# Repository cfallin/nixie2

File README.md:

# GPS-synchronized Nixie tube clock

This is a custom-designed (custom circuit design / PCB boards and custom
microcontroller firmware) digital clock. It receives the time from a GPS
receiver board, adjusts for an user-selectable timezone, and displays the time
on "Nixie tubes". A [nixie tube](https://en.wikipedia.org/wiki/Nixie_tube) is a
cold-cathode vacuum tube display technology: it uses high voltage (about 160
volts in this design) applied to an electrode in the shape of a digit in order
to display a number in brilliant glowing orange. It really is quite
mesmerizing!

This repo contains custom circuit board layouts for the main clock board and a
separate adapter sub-board for each Nixie tube. The sub-boards are designed for
IN-14 tubes (which can currently be found on eBay or Etsy for ~$20 each), but
could be adapted for IN-12, IN-18, or some other size.

The main board contains an AVR ATmega8 microcontroller, a 20MHz crystal,
several 74HC595 shift registers to expand the AVR's IO, and six KI155ID1
open-collector high voltage driver chips.

The board interfaces with a separate high-voltage DC-DC power supply, because
designing such a supply to be efficient is quite hard and I do not possess the
analog black magic skills! I bought [this
one](https://www.amazon.com/gp/product/B09D94N3MX) for $11. You can substitute
any suitable source of ~160V DC rated for about 4mA per tube (24mA total, or
just under 4 watts).

GPS is also black magic, so I bought a pre-designed GPS receiver module
[here](https://www.amazon.com/gp/product/B07P8YMVNT) for $12, and an external
active antenna [here](https://www.amazon.com/gp/product/B083D59N55) for $11.
The module provides a 1Hz "pulse-per-second" precision output and a 9600bps
serial line providing time, position, and satellite lock information using the
[NMEA](https://en.wikipedia.org/wiki/NMEA_0183) protocol. You can substitute
any GPS receiver that provides a PPS output and NMEA signal.

The ATmega8 runs firmware that decodes the NMEA to get an initial time
(synchronizing whenever a valid NMEA packet with a timestamp is received). It
measures the internal crystal oscillator against the PPS and then ticks based
on the main CPU clock, calibrated with this ticks-per-PPS value. This allows
the clock to receive the time when GPS signal is available, learn how fast or
slow its own internal oscillator is running, and then continue to keep time
when the GPS signal is lost. Whenever it comes back, time will resynchronize
automatically.

There is a simple user interface consisting of four buttons. The leftmost (SW4
on the main board) switches between time mode and set-timezone mode. In the
latter, SW2 decrements TZ offset hour and SW1 increments TZ offset hour.
(Half-hour or 15 minute timezone offsets are not yet supported; I know these
timezones exist, sorry! Happy to take PRs if anyone in such a timezone builds
this clock!)

Total cost for the clock, not including the one-time tool purchases I made
(e.g. an AVR programmer) or the scrap wood, glue, etc. for the very janky base,
and definitely not including my time, was about $230:

- $42 for the PCBs (mainboard and 6x nixie tube adapters) at Aisler.net
- $90 for the six IN-14s, on Etsy
- $22 for the KI155ID1 driver chips
- $12 for the GPS receiver
- $11 for the GPS antenna
- $11 for the 160V DC supply
- about $40 for the ATmega8, 20MHz crystal, 74HC595s, a few resistors and
  capacitors, pin headers, wire, etc.

I started thinking about building a Nixie clock in 2014, but started working on
this design regularly in Nov 2021. It first displayed a GPS-synchronized time
on Jan 6, 2022. I'd like to improve the UI a bit (allow a non-GPS
locally-set-time mode as well), and definitely improve the casing, but it suits
me well enough for now! I finally know what time it is!

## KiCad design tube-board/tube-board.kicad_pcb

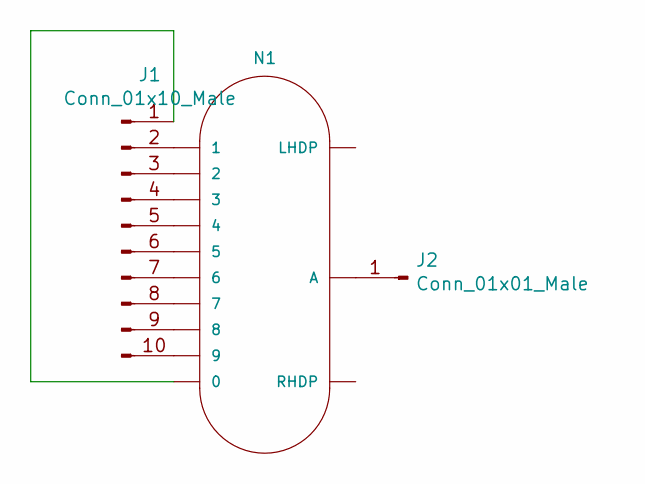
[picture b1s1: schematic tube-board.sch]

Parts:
J1: Conn_01x10_Male; PinHeader_1x10_P2.54mm_Vertical
J2: Conn_01x01_Male; PinHeader_1x01_P2.54mm_Vertical
N1: IN-14

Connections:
unnamed: J1.1, N1.0
unnamed: J1.2, N1.1
unnamed: J1.3, N1.2
unnamed: J1.4, N1.3
unnamed: J1.5, N1.4
unnamed: J1.6, N1.5
unnamed: J1.7, N1.6
unnamed: J1.8, N1.7
unnamed: J1.9, N1.8
unnamed: J1.10, N1.9
unnamed: J2.1, N1.A

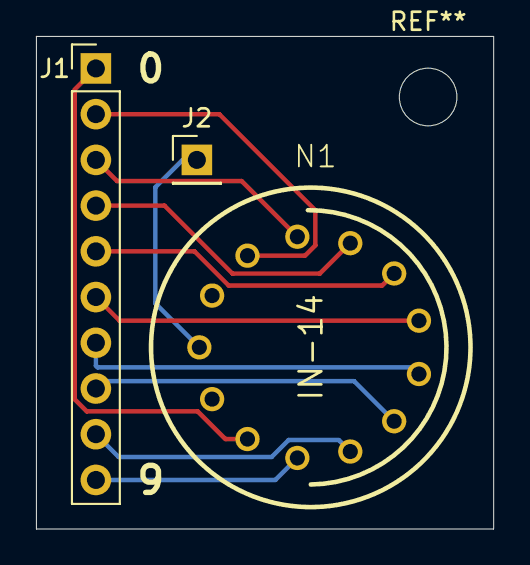
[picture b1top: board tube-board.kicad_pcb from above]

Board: 2 copper layers, 25.4 x 27.4 mm, 3 parts (0 on the bottom side), 11 nets.

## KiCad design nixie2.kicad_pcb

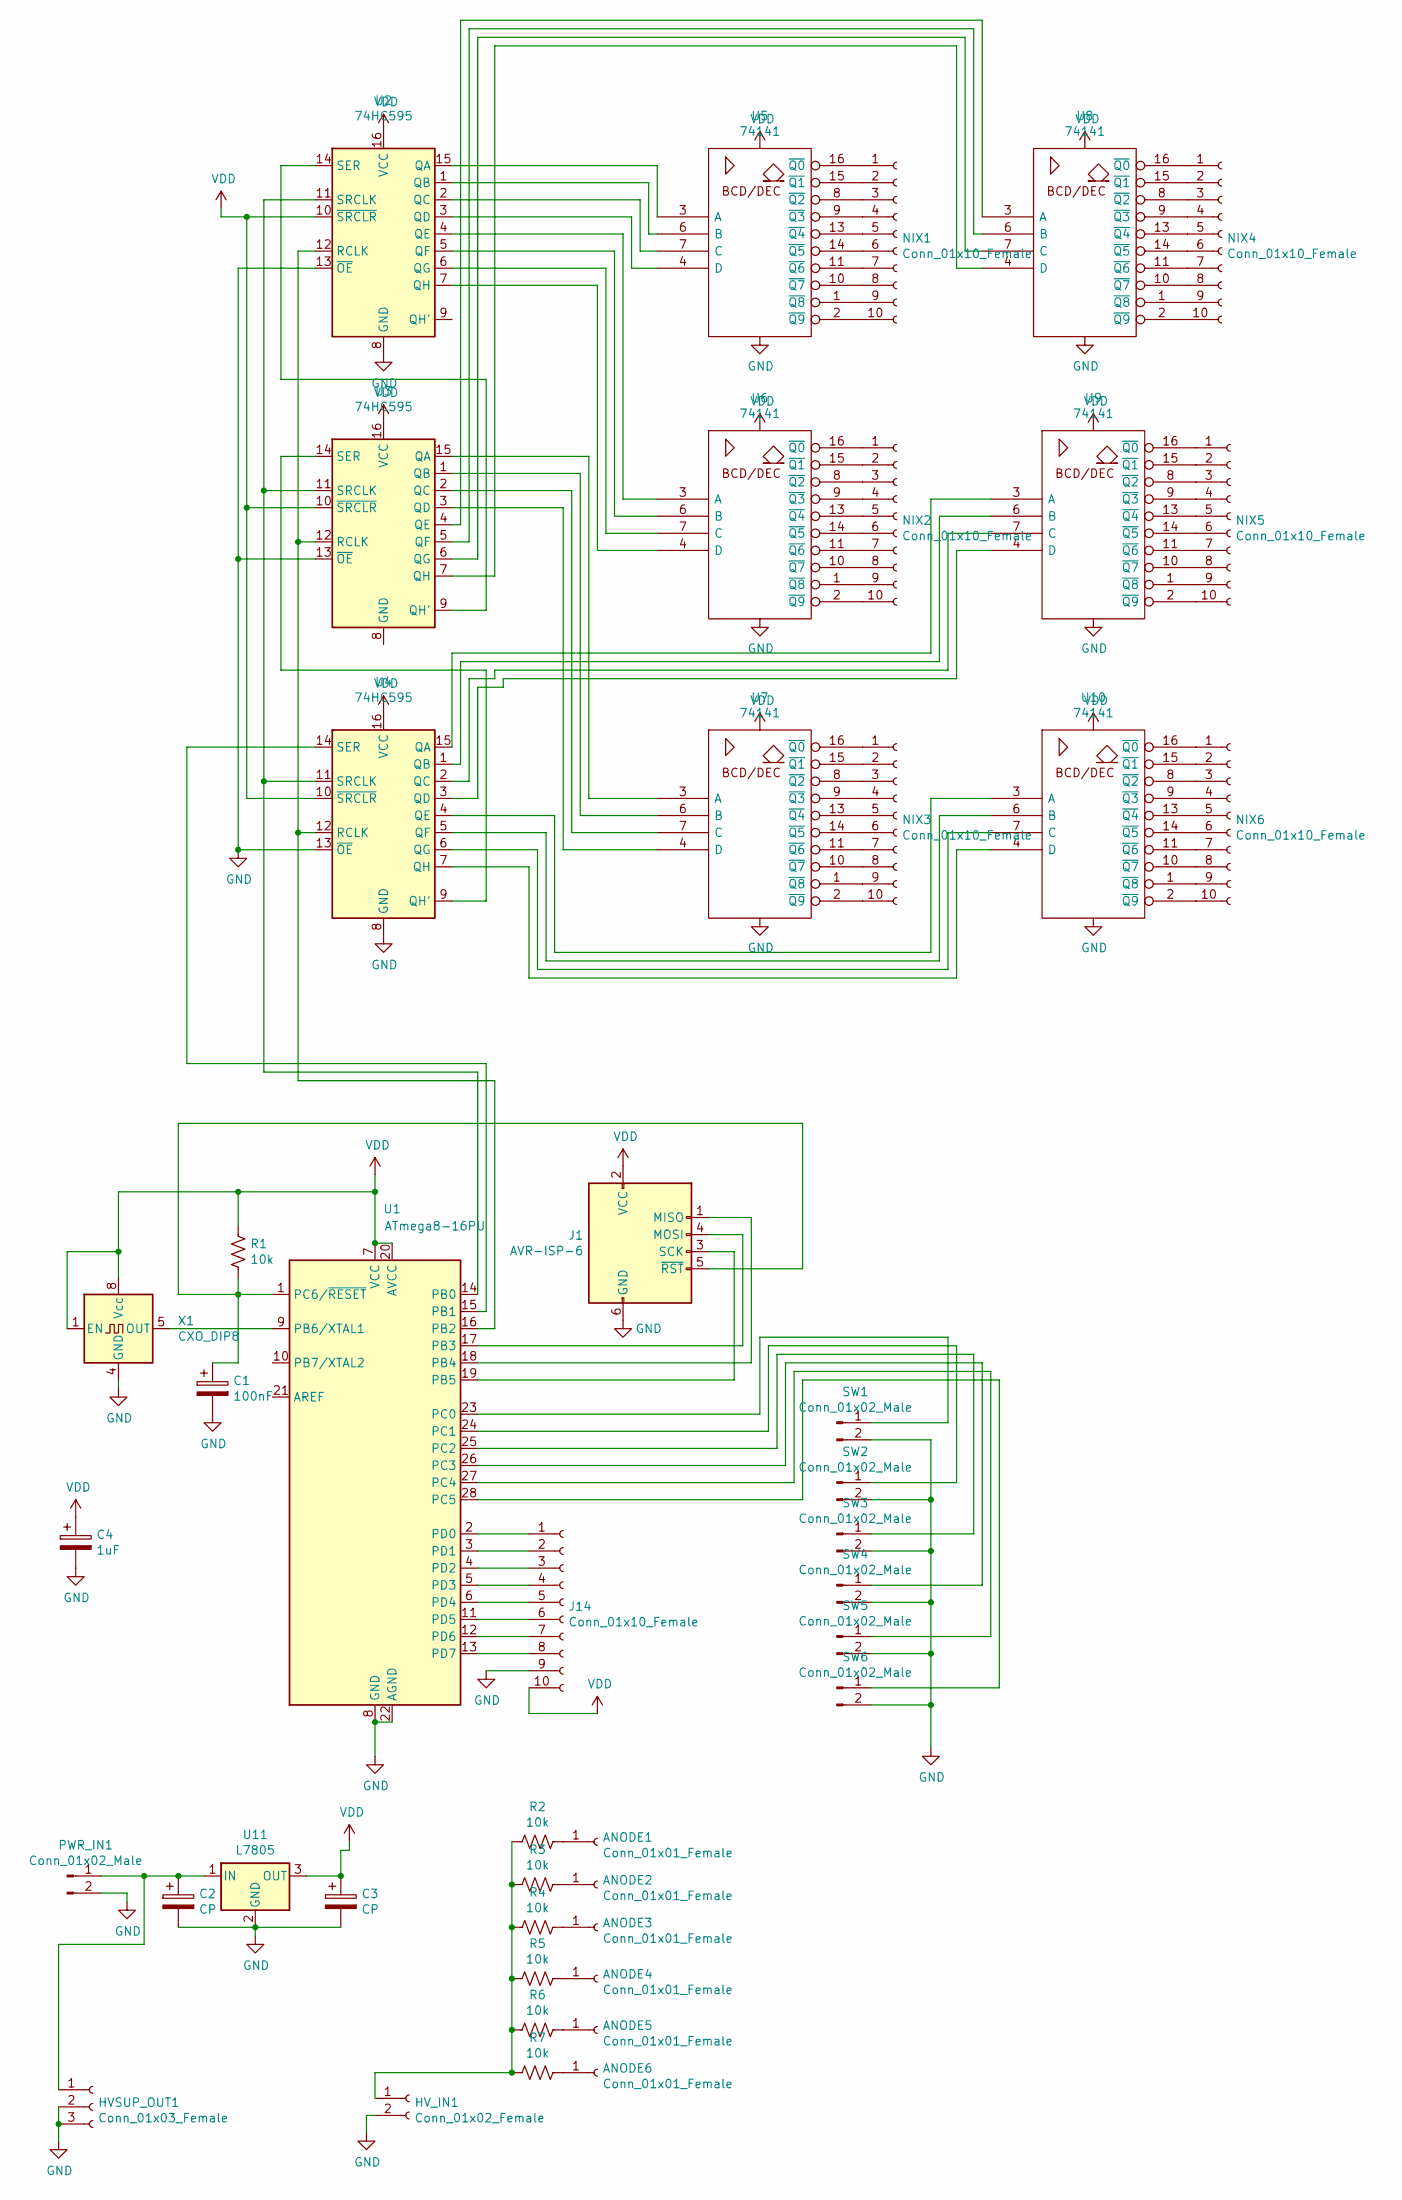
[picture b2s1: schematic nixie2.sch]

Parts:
ANODE1, ANODE2, ANODE3, ANODE4, ANODE5, ANODE6: Conn_01x01_Female; PinHeader_1x01_P2.54mm_Vertical
C1: 100nF; CP_Radial_Tantal_D5.5mm_P2.50mm
C2, C3: CP; CP_Radial_D10.0mm_P2.50mm
C4: 1uF; CP_Radial_D4.0mm_P1.50mm
HVSUP_OUT1: Conn_01x03_Female; PinHeader_1x03_P2.54mm_Vertical
HV_IN1: Conn_01x02_Female; PinHeader_1x02_P2.54mm_Vertical
J1: AVR-ISP-6; PinHeader_2x03_P2.54mm_Vertical
J14: Conn_01x10_Female; PinHeader_1x10_P2.54mm_Vertical
NIX1, NIX2, NIX3, NIX4, NIX5, NIX6: Conn_01x10_Female; PinHeader_1x10_P2.54mm_Vertical
PWR_IN1: Conn_01x02_Male; PinHeader_1x02_P2.54mm_Vertical
R1: 10k; R_Axial_DIN0207_L6.3mm_D2.5mm_P2.54mm_Vertical
R2, R3, R4, R5, R6, R7: 10k; R_Axial_DIN0207_L6.3mm_D2.5mm_P7.62mm_Horizontal
SW1, SW2, SW3, SW4, SW5, SW6: Conn_01x02_Male; PinHeader_1x02_P2.54mm_Vertical
U1: ATmega8-16PU; DIP-28_W7.62mm
U2, U3, U4: 74HC595; DIP-16_W7.62mm
U5, U6, U7, U8, U9, U10: 74141; DIP-16_W7.62mm
U11: L7805; TO-220-3_Vertical
X1: CXO_DIP8; Oscillator_DIP-8

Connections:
GND: C1.2, C2.2, C3.2, C4.2, HVSUP_OUT1.2, HVSUP_OUT1.3, HV_IN1.2, J1.6 (GND), J14.9, PWR_IN1.2, SW1.2, SW2.2, SW3.2, SW4.2, SW5.2, SW6.2, U1.8 (GND), U1.22 (AGND), U2.8 (GND), U2.13 (~OE), U3.13 (~OE), U4.8 (GND), U4.13 (~OE), U5.12 (GND), U6.12 (GND), U7.12 (GND), U8.12 (GND), U9.12 (GND), U10.12 (GND), U11.2 (GND), X1.4 (GND)
unnamed: ANODE1.1, R2.1
unnamed: ANODE2.1, R3.1
unnamed: ANODE3.1, R4.1
unnamed: ANODE4.1, R5.1
unnamed: ANODE5.1, R6.1
unnamed: ANODE6.1, R7.1
unnamed: C1.1, J1.5 (~RST), R1.2, U1.1 (PC6/~RESET)
unnamed: C2.1, HVSUP_OUT1.1, PWR_IN1.1, U11.1 (IN)
unnamed: HV_IN1.1, R2.2, R3.2, R4.2, R5.2, R6.2, R7.2
unnamed: J1.1 (MISO), U1.18 (PB4)
unnamed: J1.3 (SCK), U1.19 (PB5)
unnamed: J1.4 (MOSI), U1.17 (PB3)
unnamed: J14.1, U1.2 (PD0)
unnamed: J14.2, U1.3 (PD1)
unnamed: J14.3, U1.4 (PD2)
unnamed: J14.4, U1.5 (PD3)
unnamed: J14.5, U1.6 (PD4)
unnamed: J14.6, U1.11 (PD5)
unnamed: J14.7, U1.12 (PD6)
unnamed: J14.8, U1.13 (PD7)
unnamed: NIX1.1, U5.16 (~Q0)
unnamed: NIX1.2, U5.15 (~Q1)
unnamed: NIX1.3, U5.8 (~Q2)
unnamed: NIX1.4, U5.9 (~Q3)
unnamed: NIX1.5, U5.13 (~Q4)
unnamed: NIX1.6, U5.14 (~Q5)
unnamed: NIX1.7, U5.11 (~Q6)
unnamed: NIX1.8, U5.10 (~Q7)
unnamed: NIX1.9, U5.1 (~Q8)
unnamed: NIX1.10, U5.2 (~Q9)
unnamed: NIX2.1, U6.16 (~Q0)
unnamed: NIX2.2, U6.15 (~Q1)
unnamed: NIX2.3, U6.8 (~Q2)
unnamed: NIX2.4, U6.9 (~Q3)
unnamed: NIX2.5, U6.13 (~Q4)
unnamed: NIX2.6, U6.14 (~Q5)
unnamed: NIX2.7, U6.11 (~Q6)
unnamed: NIX2.8, U6.10 (~Q7)
unnamed: NIX2.9, U6.1 (~Q8)
unnamed: NIX2.10, U6.2 (~Q9)
unnamed: NIX3.1, U7.16 (~Q0)
unnamed: NIX3.2, U7.15 (~Q1)
unnamed: NIX3.3, U7.8 (~Q2)
unnamed: NIX3.4, U7.9 (~Q3)
unnamed: NIX3.5, U7.13 (~Q4)
unnamed: NIX3.6, U7.14 (~Q5)
unnamed: NIX3.7, U7.11 (~Q6)
unnamed: NIX3.8, U7.10 (~Q7)
unnamed: NIX3.9, U7.1 (~Q8)
unnamed: NIX3.10, U7.2 (~Q9)
unnamed: NIX4.1, U8.16 (~Q0)
unnamed: NIX4.2, U8.15 (~Q1)
unnamed: NIX4.3, U8.8 (~Q2)
unnamed: NIX4.4, U8.9 (~Q3)
unnamed: NIX4.5, U8.13 (~Q4)
unnamed: NIX4.6, U8.14 (~Q5)
unnamed: NIX4.7, U8.11 (~Q6)
unnamed: NIX4.8, U8.10 (~Q7)
unnamed: NIX4.9, U8.1 (~Q8)
unnamed: NIX4.10, U8.2 (~Q9)
unnamed: NIX5.1, U9.16 (~Q0)
unnamed: NIX5.2, U9.15 (~Q1)
unnamed: NIX5.3, U9.8 (~Q2)
unnamed: NIX5.4, U9.9 (~Q3)
unnamed: NIX5.5, U9.13 (~Q4)
unnamed: NIX5.6, U9.14 (~Q5)
unnamed: NIX5.7, U9.11 (~Q6)
unnamed: NIX5.8, U9.10 (~Q7)
unnamed: NIX5.9, U9.1 (~Q8)
unnamed: NIX5.10, U9.2 (~Q9)
unnamed: NIX6.1, U10.16 (~Q0)
unnamed: NIX6.2, U10.15 (~Q1)
unnamed: NIX6.3, U10.8 (~Q2)
unnamed: NIX6.4, U10.9 (~Q3)
unnamed: NIX6.5, U10.13 (~Q4)
unnamed: NIX6.6, U10.14 (~Q5)
unnamed: NIX6.7, U10.11 (~Q6)
unnamed: NIX6.8, U10.10 (~Q7)
unnamed: NIX6.9, U10.1 (~Q8)
unnamed: NIX6.10, U10.2 (~Q9)
unnamed: SW1.1, U1.23 (PC0)
unnamed: SW2.1, U1.24 (PC1)
unnamed: SW3.1, U1.25 (PC2)
unnamed: SW4.1, U1.26 (PC3)
unnamed: SW5.1, U1.27 (PC4)
unnamed: SW6.1, U1.28 (PC5)
unnamed: U1.9 (PB6/XTAL1), X1.5 (OUT)
unnamed: U1.14 (PB0), U2.11 (SRCLK), U3.11 (SRCLK), U4.11 (SRCLK)
unnamed: U1.15 (PB1), U4.14 (SER)
unnamed: U1.16 (PB2), U2.12 (RCLK), U3.12 (RCLK), U4.12 (RCLK)
unnamed: U2.1 (QB), U5.6 (B)
unnamed: U2.2 (QC), U5.7 (C)
unnamed: U2.3 (QD), U5.4 (D)
unnamed: U2.4 (QE), U6.3 (A)
unnamed: U2.5 (QF), U6.6 (B)
unnamed: U2.6 (QG), U6.7 (C)
unnamed: U2.7 (QH), U6.4 (D)
unnamed: U2.14 (SER), U3.9 (QH')
unnamed: U2.15 (QA), U5.3 (A)
unnamed: U3.1 (QB), U7.6 (B)
unnamed: U3.2 (QC), U7.7 (C)
unnamed: U3.3 (QD), U7.4 (D)
unnamed: U3.4 (QE), U8.3 (A)
unnamed: U3.5 (QF), U8.6 (B)
unnamed: U3.6 (QG), U8.7 (C)
unnamed: U3.7 (QH), U8.4 (D)
unnamed: U3.14 (SER), U4.9 (QH')
unnamed: U3.15 (QA), U7.3 (A)
unnamed: U4.1 (QB), U9.6 (B)
unnamed: U4.2 (QC), U9.7 (C)
unnamed: U4.3 (QD), U9.4 (D)
unnamed: U4.15 (QA), U9.3 (A)
unnamed: U4.4 (QE), U10.3 (A)
unnamed: U4.7 (QH), U10.4 (D)
unnamed: U4.5 (QF), U10.6 (B)
unnamed: U4.6 (QG), U10.7 (C)
VCC: C3.1, C4.1, J1.2 (VCC), J14.10, R1.1, U1.7 (VCC), U1.20 (AVCC), U2.10 (~SRCLR), U2.16 (VCC), U3.10 (~SRCLR), U3.16 (VCC), U4.10 (~SRCLR), U4.16 (VCC), U5.5 (VCC), U6.5 (VCC), U7.5 (VCC), U8.5 (VCC), U9.5 (VCC), U10.5 (VCC), U11.3 (OUT), X1.1 (EN), X1.8 (Vcc)

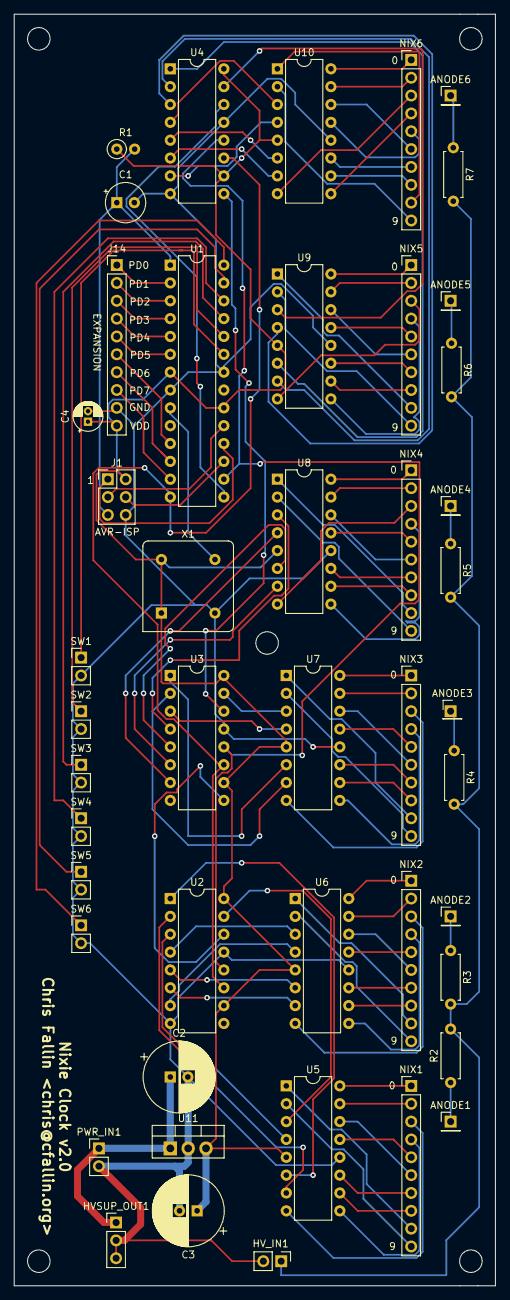
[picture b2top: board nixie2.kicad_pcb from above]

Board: 2 copper layers, 68.5 x 181.0 mm, 46 parts (0 on the bottom side), 118 nets.

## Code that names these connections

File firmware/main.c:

/*
 * Nixie Clock v2.0
 *
 * Copyright (c) 2022 Chris Fallin <chris@cfallin.org>
 * Placed under the Apache-2.0 license.
 */

/* 
 * Assume an ATmega8.
 *
 * IO connections (manufactured board version):
 *
 * PB0 is shift register clock (active high to shift).
 * PB1 is shift register data.
 * PB2 is shift register latch (active high to latch).
 *
 * Shift register output is nixie 2, 1; 4, 3; 6, 5. MSB first of BCD digits.
 *
 * PC0..PC5 are switches 0..5 (to ground; need internal pullups).
 *
 * PD0..PD7 are expansion port.
 */

#include <avr/interrupt.h>

#include "nixie.h"

#define EXPECTED_TIMER_TICKS_PER_SEC 78125 // 20MHz / 256

long timer_ticks = 0;
long hz = EXPECTED_TIMER_TICKS_PER_SEC;
uint8_t time_h = 0, time_m = 0, time_s = 0;

#define DISPLAY_TIME 0
#define DISPLAY_SET 1
#define DISPLAY_CAL 2
int display_mode = 0;

#define UI_TIME 0
#define UI_TO_SET 1
#define UI_SET 2
#define UI_SET_NEXT 3
#define UI_SET_PLUS 4
#define UI_SET_MINUS 5

#define UI_TO_SET_CAL 6
#define UI_SET_CAL 7
#define UI_SET_CAL_NEXT 8
#define UI_SET_CAL_PLUS 9
#define UI_SET_CAL_MINUS 10
#define UI_TO_TIME 11

int ui_state = 0;
int ui_set_digit = 0;

void do_ui() {

    switch (ui_state) {
    case UI_TIME:
        display_mode = DISPLAY_TIME;
        if (switches & 8) {
            ui_state = UI_TO_SET;
        }
        break;
    case UI_TO_SET:
        display_mode = DISPLAY_TIME;
        if (!(switches & 8)) {
            ui_state = UI_SET;
            ui_set_digit = 0;
        }
        break;
    case UI_SET:
        display_mode = DISPLAY_SET;
        if (switches & 8) {
            ui_state = UI_TO_SET_CAL;
        } else if (switches & 4) {
            ui_set_digit++;
            if (ui_set_digit == 3) {
                ui_set_digit = 0;
            }
            ui_state = UI_SET_NEXT;
        } else if (switches & 2) {
            switch (ui_set_digit) {
                case 0:
                    time_h++;
                    if (time_h == 24) {
                        time_h = 0;
                    }
                    break;
                case 1:
                    time_m++;
                    if (time_m == 60) {
                        time_m = 0;
                    }
                    break;
                case 2:
                    time_s++;
                    if (time_s == 60) {
                        time_s = 0;
                    }
                    break;
            }
            ui_state = UI_SET_PLUS;
        } else if (switches & 1) {
            switch (ui_set_digit) {
                case 0:
                    if (time_h == 0) {
                        time_h = 24;
                    }
                    time_h--;
                    break;
                case 1:
                    if (time_m == 0) {
                        time_m = 60;
                    }
                    time_m--;
                    break;
                case 2:
                    if (time_s == 0) {
                        time_s = 60;
                    }
                    time_s--;
                    break;
            }
            ui_state = UI_SET_MINUS;
        }
        break;
    case UI_SET_NEXT:
        display_mode = DISPLAY_SET;
        if (!(switches & 4)) {
            ui_state = UI_SET;
        }
        break;
    case UI_SET_PLUS:
        display_mode = DISPLAY_SET;
        if (switches & 1) {
            switch (ui_set_digit) {
                case 0:
                    time_h = 0;
                    break;
                case 1:
                    time_m = 0;
                    break;
                case 2:
                    time_s = 0;
                    break;
            }
        } else if (!(switches & 2)) {
            ui_state = UI_SET;
        }
        break;
    case UI_SET_MINUS:
        display_mode = DISPLAY_SET;
        if (switches & 2) {
            switch (ui_set_digit) {
                case 0:
                    time_h = 0;
                    break;
                case 1:
                    time_m = 0;
                    break;
                case 2:
                    time_s = 0;
                    break;
            }
        } else if (!(switches & 1)) {
            ui_state = UI_SET;
        }
        break;
    case UI_TO_SET_CAL:
        display_mode = DISPLAY_SET;
        if (!(switches & 8)) {
            ui_state = UI_SET_CAL;
            ui_set_digit = 0;
        }
        break;
    case UI_SET_CAL:
        display_mode = DISPLAY_CAL;
        if (switches & 8) {
            ui_state = UI_TO_TIME;
        } else if (switches & 4) {
            ui_set_digit++;
            if (ui_set_digit == 5) {
                ui_set_digit = 0;
            }
            ui_state = UI_SET_CAL_NEXT;
        } else if (switches & 2) {
            int amt = 1;
            for (int i = 0; i < (4 - ui_set_digit); i++) {
                amt *= 10;
            }
            hz += amt;
            if (hz > 100000) {
                hz -= 100000;
            }
            ui_state = UI_SET_CAL_PLUS;
        } else if (switches & 1) {
            int amt = 1;
            for (int i = 0; i < (4 - ui_set_digit); i++) {
                amt *= 10;
            }
            hz -= amt;
            if (hz < amt) {
                hz += 100000;
            }
            ui_state = UI_SET_CAL_MINUS;
        }
        break;
    case UI_SET_CAL_NEXT:
        display_mode = DISPLAY_CAL;
        if (!(switches & 4)) {
            ui_state = UI_SET_CAL;
        }
        break;
    case UI_SET_CAL_PLUS:
        display_mode = DISPLAY_CAL;
        if (!(switches & 2)) {
            ui_state = UI_SET_CAL;
        }
        break;
    case UI_SET_CAL_MINUS:
        display_mode = DISPLAY_CAL;
        if (!(switches & 1)) {
            ui_state = UI_SET_CAL;
        }
        break;
    case UI_TO_TIME:
        display_mode = DISPLAY_CAL;
        if (!(switches & 8)) {
            ui_state = UI_TIME;
        }
        break;
    }
}

void update_display() {
    switch (display_mode) {
    case DISPLAY_TIME: {
        display_digits(time_h / 10, time_h % 10, time_m / 10, time_m % 10, time_s / 10, time_s % 10);
        break;
    }
    case DISPLAY_SET: {
        int second_half_second = timer_ticks > (hz / 2);
        int h1 = 15, h2 = 15, m1 = 15, m2 = 15, s1 = 15, s2 = 15;

        if (ui_set_digit != 0 || !second_half_second) {
            h1 = time_h / 10;
            h2 = time_h % 10;
        }
        if (ui_set_digit != 1 || !second_half_second) {
            m1 = time_m / 10;
            m2 = time_m % 10;
        }
        if (ui_set_digit != 2 || !second_half_second) {
            s1 = time_s / 10;
            s2 = time_s % 10;
        }
        display_digits(h1, h2, m1, m2, s1, s2);
        break;
    }
    case DISPLAY_CAL: {
        int second_half_second = timer_ticks > (hz / 2);
        int d1 = 15, d2 = 15, d3 = 15, d4 = 15, d5 = 15;

        if (ui_set_digit != 0 || !second_half_second) {
            d1 = (hz / 10000) % 10;
        }
        if (ui_set_digit != 1 || !second_half_second) {
            d2 = (hz / 1000) % 10;
        }
        if (ui_set_digit != 2 || !second_half_second) {
            d3 = (hz / 100) % 10;
        }
        if (ui_set_digit != 3 || !second_half_second) {
            d4 = (hz / 10) % 10;
        }
        if (ui_set_digit != 4 || !second_half_second) {
            d5 = hz % 10;
        }
        display_digits(15, d1, d2, d3, d4, d5);
    }
    }
}

int main()
{
    init_display();
#ifdef GPS
    init_usart();
    enable_int0();
#endif
    init_switches();
    enable_timer_interrupt();
    sei();

    int pos = 0;
    int state = 0;
    while (1) {
        delay();
        read_switches();
        do_ui();
        update_display();
    }
}

void do_pps() {
}

void do_second() {
    time_s++;
    if (time_s == 60) {
        time_s = 0;
        time_m++;
    }
    if (time_m == 60) {
        time_m = 0;
        time_h++;
    }
    if (time_h == 24) {
        time_h = 0;
    }
}

void do_timer_int() {
    timer_ticks++;
    if (timer_ticks >= hz) {
        timer_ticks = 0;
        do_second();
    }
}

void do_gps_time(int _h1, int _h2, int _m1, int _m2, int _s1, int _s2) {
#ifdef GPS
    h1 = _h1;
    h2 = _h2;
    m1 = _m1;
    m2 = _m2;
    s1 = _s1;
    s2 = _s2;
#endif
}

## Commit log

2021-11-29 Initial commit: nixie2 board.
2021-11-29 Update.
2021-11-30 Add tube adapter board, and tweak main board
2021-11-30 Add some mounting holes
2021-11-30 Remove extraneous label on mounting hole.
2021-11-30 Move HV_IN connector to not interfere with NIX1 sub-board.
2021-11-30 Minor changes to power traces; also remove parallel run between clock line and ISP line.
2021-11-30 tweak tube board height to not cut off silkscreen
2022-01-05 Initial test firmware
2022-01-06 Switch debouncing, UART setup, and PPS interrupt
2022-01-06 working clock holy shit
2022-01-06 manually convert to PST for now
2022-01-07 fix TZ adjustment
2022-01-31 Basic timekeeping, fallback to local osc if no GPS timestamp, discipline of local osc against GPS PPS, and timezone setting interface
2022-01-31 README.
2022-01-31 remove GPS-disciplined-local-oscillator logic for now; need to refine interactions with GPS time sync
2022-02-20 clock firmware: remove GPS interface for now (unreliable reception); button UI for setting local time
2022-02-22 Support time-setting via serial input.
2022-02-22 Add simple daemon that syncs clock over serial port.
2022-02-22 add systemd unit file for nixie clock service
2022-02-25 Restart nixie-clock daemon; otherwise it will die on spurious USB errors and clock will silently drift off true time
2022-03-03 fix time divergence once and for all: daemon updates clock time over serial continuously
